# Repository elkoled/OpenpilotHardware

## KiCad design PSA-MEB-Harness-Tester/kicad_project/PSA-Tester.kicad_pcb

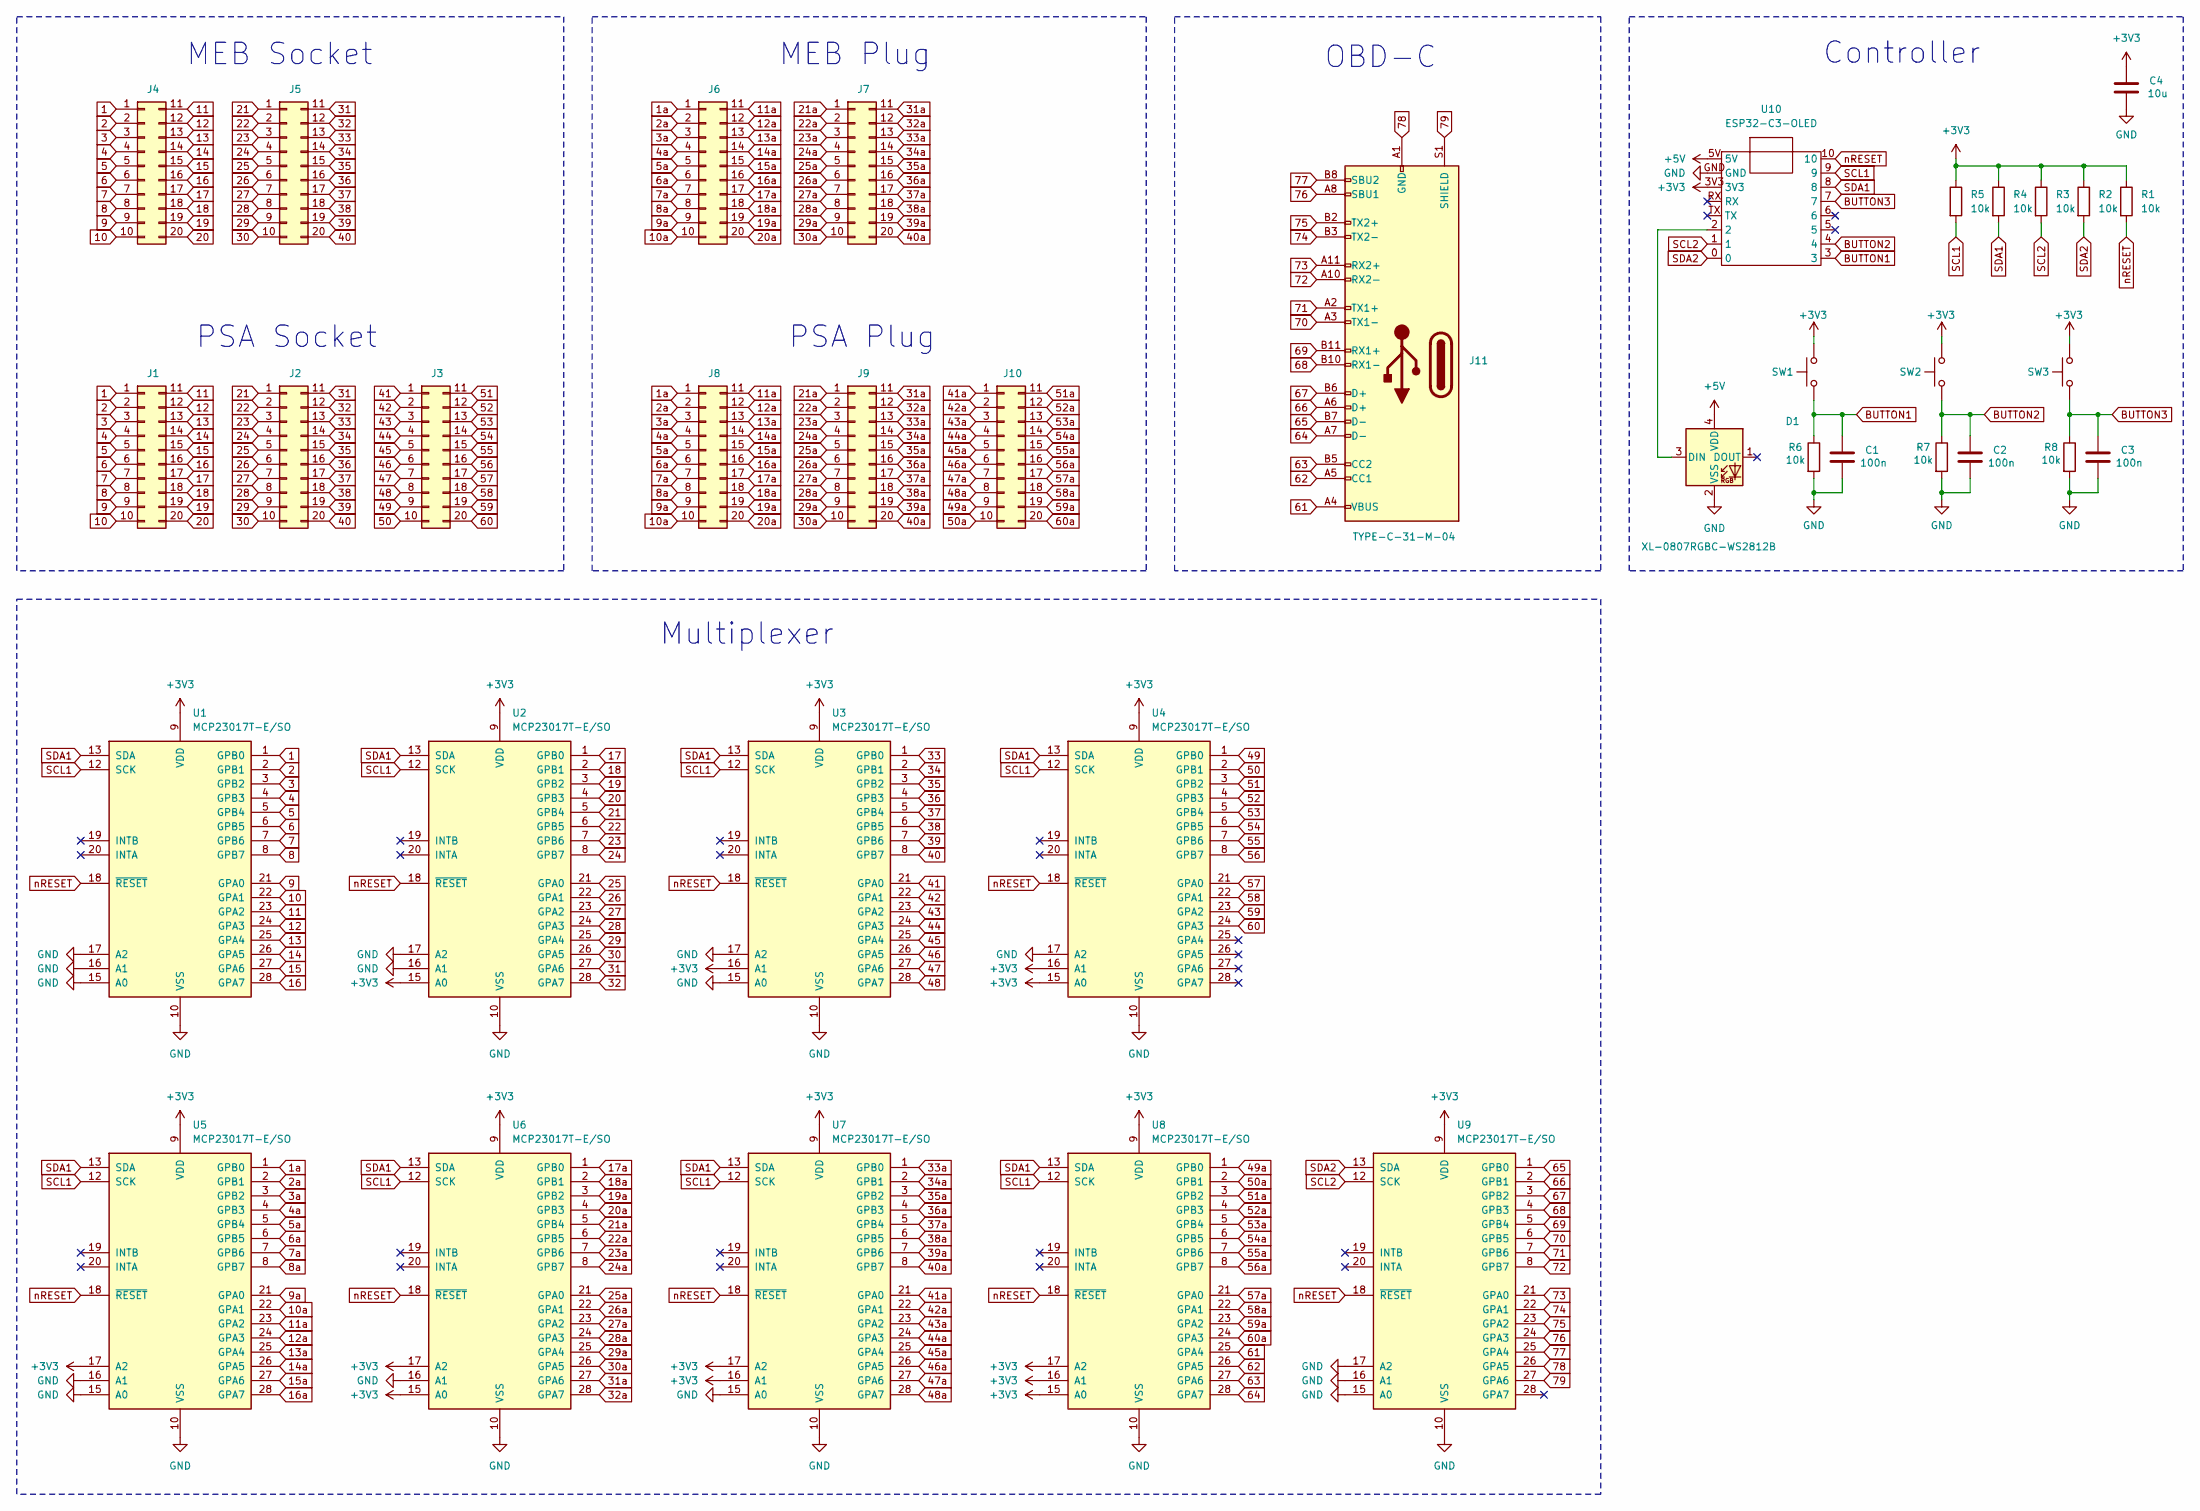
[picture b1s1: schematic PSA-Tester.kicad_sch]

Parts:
C1, C2, C3: 100n; C_1206_3216Metric_Pad1.33x1.80mm_HandSolder
C4: 10u; C_1206_3216Metric_Pad1.33x1.80mm_HandSolder
D1: XL-0807RGBC-WS2812B; LED_WS2812B-2020_PLCC4_2.0x2.0mm
J1, J2, J3, J4, J5, J6, J7, J8, J9, J10: PinHeader_2x10_P2.54mm_Vertical
J11: TYPE-C-31-M-04
R1, R2, R3, R4, R5, R6, R7, R8: 10k; R_1206_3216Metric_Pad1.30x1.75mm_HandSolder
SW1, SW2, SW3: TS-1057S-03126; SW_SPST_Omron_B3FS-101xP
U1, U2, U3, U4, U5, U6, U7, U8, U9: MCP23017T-E/SO; SOIC-28W_7.5x18.7mm_P1.27mm
U10: ESP32-C3-OLED

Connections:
1: J1.1, J4.1, U1.1 (GPB0)
1a: J6.1, J8.1, U5.1 (GPB0)
2: J1.2, J4.2, U1.2 (GPB1)
2a: J6.2, J8.2, U5.2 (GPB1)
3: J1.3, J4.3, U1.3 (GPB2)
3a: J6.3, J8.3, U5.3 (GPB2)
4: J1.4, J4.4, U1.4 (GPB3)
4a: J6.4, J8.4, U5.4 (GPB3)
5: J1.5, J4.5, U1.5 (GPB4)
5a: J6.5, J8.5, U5.5 (GPB4)
6: J1.6, J4.6, U1.6 (GPB5)
6a: J6.6, J8.6, U5.6 (GPB5)
7: J1.7, J4.7, U1.7 (GPB6)
7a: J6.7, J8.7, U5.7 (GPB6)
8: J1.8, J4.8, U1.8 (GPB7)
8a: J6.8, J8.8, U5.8 (GPB7)
9: J1.9, J4.9, U1.21 (GPA0)
9a: J6.9, J8.9, U5.21 (GPA0)
10: J1.10, J4.10, U1.22 (GPA1)
10a: J6.10, J8.10, U5.22 (GPA1)
11: J1.11, J4.11, U1.23 (GPA2)
11a: J6.11, J8.11, U5.23 (GPA2)
12: J1.12, J4.12, U1.24 (GPA3)
12a: J6.12, J8.12, U5.24 (GPA3)
13: J1.13, J4.13, U1.25 (GPA4)
13a: J6.13, J8.13, U5.25 (GPA4)
14: J1.14, J4.14, U1.26 (GPA5)
14a: J6.14, J8.14, U5.26 (GPA5)
15: J1.15, J4.15, U1.27 (GPA6)
15a: J6.15, J8.15, U5.27 (GPA6)
16: J1.16, J4.16, U1.28 (GPA7)
16a: J6.16, J8.16, U5.28 (GPA7)
17: J1.17, J4.17, U2.1 (GPB0)
17a: J6.17, J8.17, U6.1 (GPB0)
18: J1.18, J4.18, U2.2 (GPB1)
18a: J6.18, J8.18, U6.2 (GPB1)
19: J1.19, J4.19, U2.3 (GPB2)
19a: J6.19, J8.19, U6.3 (GPB2)
20: J1.20, J4.20, U2.4 (GPB3)
20a: J6.20, J8.20, U6.4 (GPB3)
21: J2.1, J5.1, U2.5 (GPB4)
21a: J7.1, J9.1, U6.5 (GPB4)
22: J2.2, J5.2, U2.6 (GPB5)
22a: J7.2, J9.2, U6.6 (GPB5)
23: J2.3, J5.3, U2.7 (GPB6)
23a: J7.3, J9.3, U6.7 (GPB6)
24: J2.4, J5.4, U2.8 (GPB7)
24a: J7.4, J9.4, U6.8 (GPB7)
25: J2.5, J5.5, U2.21 (GPA0)
25a: J7.5, J9.5, U6.21 (GPA0)
26: J2.6, J5.6, U2.22 (GPA1)
26a: J7.6, J9.6, U6.22 (GPA1)
27: J2.7, J5.7, U2.23 (GPA2)
27a: J7.7, J9.7, U6.23 (GPA2)
28: J2.8, J5.8, U2.24 (GPA3)
28a: J7.8, J9.8, U6.24 (GPA3)
29: J2.9, J5.9, U2.25 (GPA4)
29a: J7.9, J9.9, U6.25 (GPA4)
30: J2.10, J5.10, U2.26 (GPA5)
30a: J7.10, J9.10, U6.26 (GPA5)
31: J2.11, J5.11, U2.27 (GPA6)
31a: J7.11, J9.11, U6.27 (GPA6)
32: J2.12, J5.12, U2.28 (GPA7)
32a: J7.12, J9.12, U6.28 (GPA7)
33: J2.13, J5.13, U3.1 (GPB0)
33a: J7.13, J9.13, U7.1 (GPB0)
34: J2.14, J5.14, U3.2 (GPB1)
34a: J7.14, J9.14, U7.2 (GPB1)
35: J2.15, J5.15, U3.3 (GPB2)
35a: J7.15, J9.15, U7.3 (GPB2)
36: J2.16, J5.16, U3.4 (GPB3)
36a: J7.16, J9.16, U7.4 (GPB3)
37: J2.17, J5.17, U3.5 (GPB4)
37a: J7.17, J9.17, U7.5 (GPB4)
38: J2.18, J5.18, U3.6 (GPB5)
38a: J7.18, J9.18, U7.6 (GPB5)
39: J2.19, J5.19, U3.7 (GPB6)
39a: J7.19, J9.19, U7.7 (GPB6)
40: J2.20, J5.20, U3.8 (GPB7)
40a: J7.20, J9.20, U7.8 (GPB7)
41: J3.1, U3.21 (GPA0)
41a: J10.1, U7.21 (GPA0)
42: J3.2, U3.22 (GPA1)
42a: J10.2, U7.22 (GPA1)
43: J3.3, U3.23 (GPA2)
43a: J10.3, U7.23 (GPA2)
44: J3.4, U3.24 (GPA3)
44a: J10.4, U7.24 (GPA3)
45: J3.5, U3.25 (GPA4)
45a: J10.5, U7.25 (GPA4)
46: J3.6, U3.26 (GPA5)
46a: J10.6, U7.26 (GPA5)
47: J3.7, U3.27 (GPA6)
47a: J10.7, U7.27 (GPA6)
48: J3.8, U3.28 (GPA7)
48a: J10.8, U7.28 (GPA7)
49: J3.9, U4.1 (GPB0)
49a: J10.9, U8.1 (GPB0)
50: J3.10, U4.2 (GPB1)
50a: J10.10, U8.2 (GPB1)
51: J3.11, U4.3 (GPB2)
51a: J10.11, U8.3 (GPB2)
52: J3.12, U4.4 (GPB3)
52a: J10.12, U8.4 (GPB3)
53: J3.13, U4.5 (GPB4)
53a: J10.13, U8.5 (GPB4)
54: J3.14, U4.6 (GPB5)
54a: J10.14, U8.6 (GPB5)
55: J3.15, U4.7 (GPB6)
55a: J10.15, U8.7 (GPB6)
56: J3.16, U4.8 (GPB7)
56a: J10.16, U8.8 (GPB7)
57: J3.17, U4.21 (GPA0)
57a: J10.17, U8.21 (GPA0)
58: J3.18, U4.22 (GPA1)
58a: J10.18, U8.22 (GPA1)
59: J3.19, U4.23 (GPA2)
59a: J10.19, U8.23 (GPA2)
60: J3.20, U4.24 (GPA3)
60a: J10.20, U8.24 (GPA3)
61: J11.A4 (VBUS), J11.A9 (VBUS), J11.B4 (VBUS), J11.B9 (VBUS), U8.25 (GPA4)
62: J11.A5 (CC1), U8.26 (GPA5)
63: J11.B5 (CC2), U8.27 (GPA6)
64: J11.A7 (D-), U8.28 (GPA7)
65: J11.B7 (D-), U9.1 (GPB0)
66: J11.A6 (D+), U9.2 (GPB1)
67: J11.B6 (D+), U9.3 (GPB2)
68: J11.B10 (RX1-), U9.4 (GPB3)
69: J11.B11 (RX1+), U9.5 (GPB4)
70: J11.A3 (TX1-), U9.6 (GPB5)
71: J11.A2 (TX1+), U9.7 (GPB6)
72: J11.A10 (RX2-), U9.8 (GPB7)
73: J11.A11 (RX2+), U9.21 (GPA0)
74: J11.B3 (TX2-), U9.22 (GPA1)
75: J11.B2 (TX2+), U9.23 (GPA2)
76: J11.A8 (SBU1), U9.24 (GPA3)
77: J11.B8 (SBU2), U9.25 (GPA4)
78: J11.A1 (GND), J11.A12 (GND), J11.B1 (GND), J11.B12 (GND), U9.26 (GPA5)
79: J11.S1 (SHIELD), U9.27 (GPA6)
+3V3: C4.1, R1.1, R2.1, R3.1, R4.1, R5.1, SW1.1, SW2.1, SW3.1, U1.9 (VDD), U2.9 (VDD), U2.15 (A0), U3.9 (VDD), U3.16 (A1), U4.9 (VDD), U4.15 (A0), U4.16 (A1), U5.9 (VDD), U5.17 (A2), U6.9 (VDD), U6.15 (A0), U6.17 (A2), U7.9 (VDD), U7.16 (A1), U7.17 (A2), U8.9 (VDD), U8.15 (A0), U8.16 (A1), U8.17 (A2), U9.9 (VDD), U10.3V3
+5V: D1.4 (VDD), U10.5V
BUTTON1: C1.1, R6.1, SW1.2, U10.3
BUTTON2: C2.1, R7.1, SW2.2, U10.4
BUTTON3: C3.1, R8.1, SW3.2, U10.7
GND: C1.2, C2.2, C3.2, C4.2, D1.2 (VSS), R6.2, R7.2, R8.2, U1.10 (VSS), U1.15 (A0), U1.16 (A1), U1.17 (A2), U2.10 (VSS), U2.16 (A1), U2.17 (A2), U3.10 (VSS), U3.15 (A0), U3.17 (A2), U4.10 (VSS), U4.17 (A2), U5.10 (VSS), U5.15 (A0), U5.16 (A1), U6.10 (VSS), U6.16 (A1), U7.10 (VSS), U7.15 (A0), U8.10 (VSS), U9.10 (VSS), U9.15 (A0), U9.16 (A1), U9.17 (A2), U10.GND
unnamed: D1.3 (DIN), U10.2
SCL1: R5.2, U1.12 (SCK), U2.12 (SCK), U3.12 (SCK), U4.12 (SCK), U5.12 (SCK), U6.12 (SCK), U7.12 (SCK), U8.12 (SCK), U10.9
SCL2: R3.2, U9.12 (SCK), U10.1
SDA1: R4.2, U1.13 (SDA), U2.13 (SDA), U3.13 (SDA), U4.13 (SDA), U5.13 (SDA), U6.13 (SDA), U7.13 (SDA), U8.13 (SDA), U10.8
SDA2: R2.2, U9.13 (SDA), U10.0
nRESET: R1.2, U1.18 (~RESET), U2.18 (~RESET), U3.18 (~RESET), U4.18 (~RESET), U5.18 (~RESET), U6.18 (~RESET), U7.18 (~RESET), U8.18 (~RESET), U9.18 (~RESET), U10.10

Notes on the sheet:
Controller
OBD-C
Multiplexer
PSA Plug
MEB Plug
MEB Socket
PSA Socket

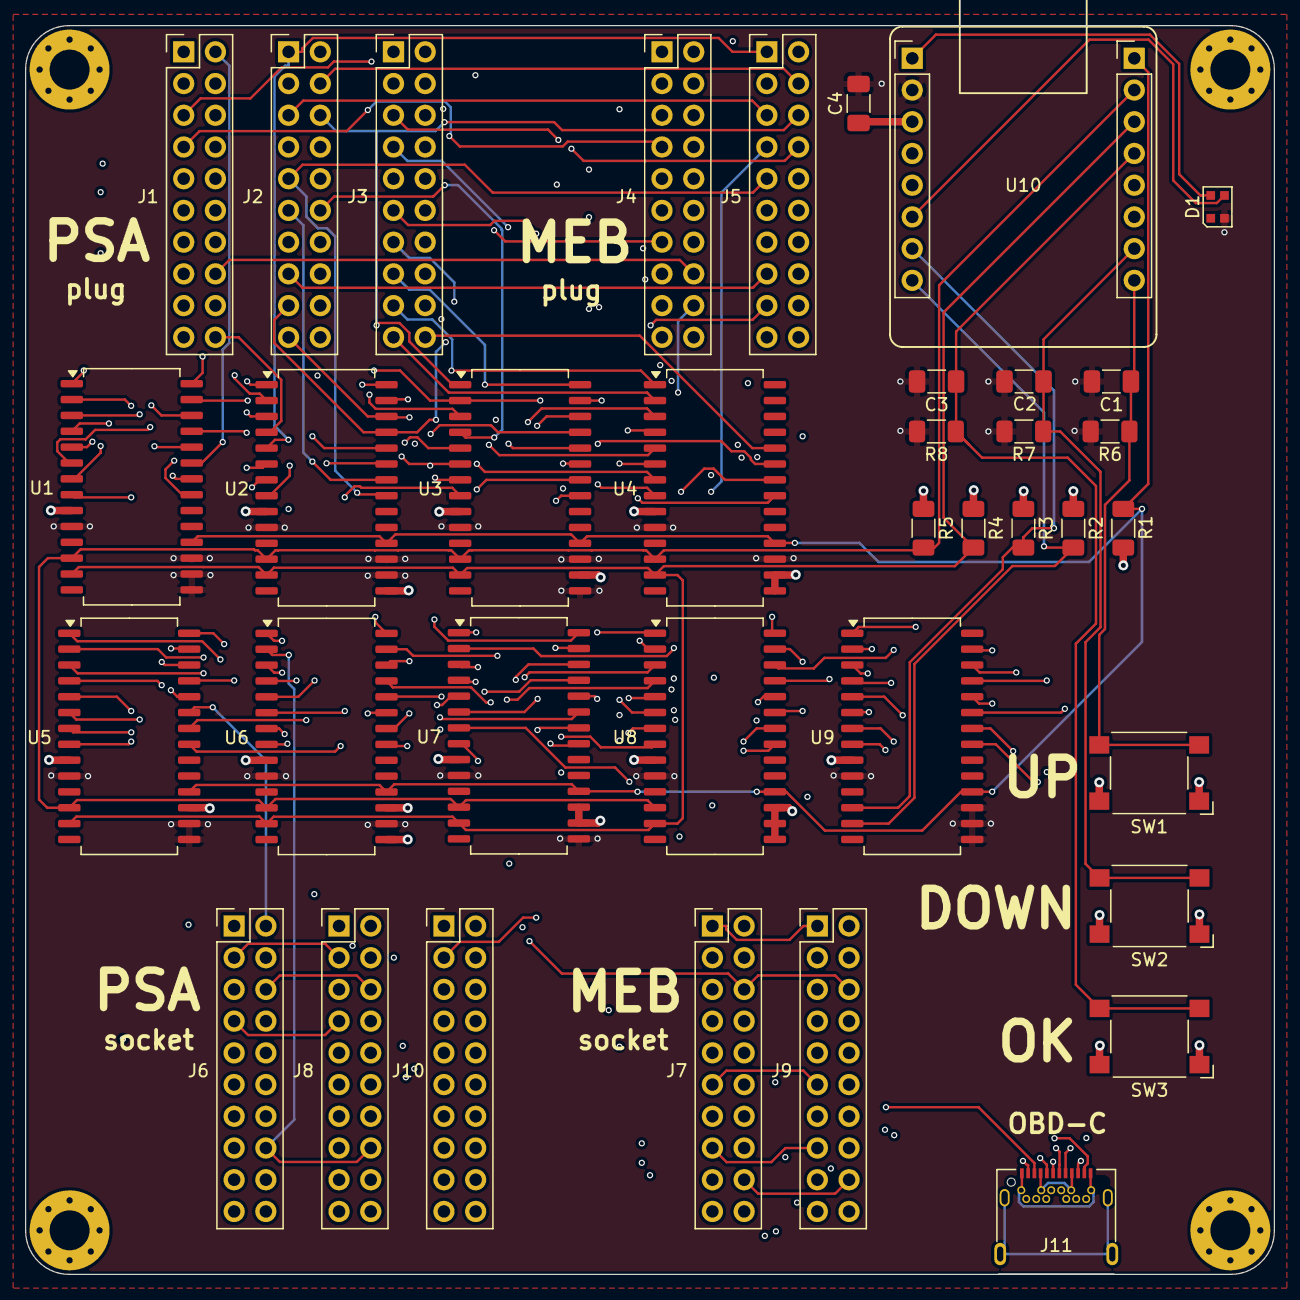
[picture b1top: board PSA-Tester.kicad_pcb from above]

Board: 4 copper layers, 100.0 x 100.0 mm, 41 parts (0 on the bottom side), 151 nets.

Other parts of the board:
REF1, REF2, REF3, REF4: MountingHole_3.2mm_M3_Pad_Via

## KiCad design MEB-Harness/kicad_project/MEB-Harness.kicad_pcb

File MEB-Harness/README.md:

# Open Source All-in-One Harness / Harnessbox for VW MEB-based vehicles equipped with a Gateway

## Compatibility list
#### Volkswagen
- ID.3
- ID.4
- ID.5
- ID.6
- ID.7
- ID.7 Tourer
- ID. Buzz
- ID. Buzz Cargo
- ID. UNYX
#### Škoda
- Enyaq
- Enyaq Coupé
- Elroq
#### Cupra
- Born
- Tavascan

The device is in development

If you have any questions contact me on Discord: elkoled

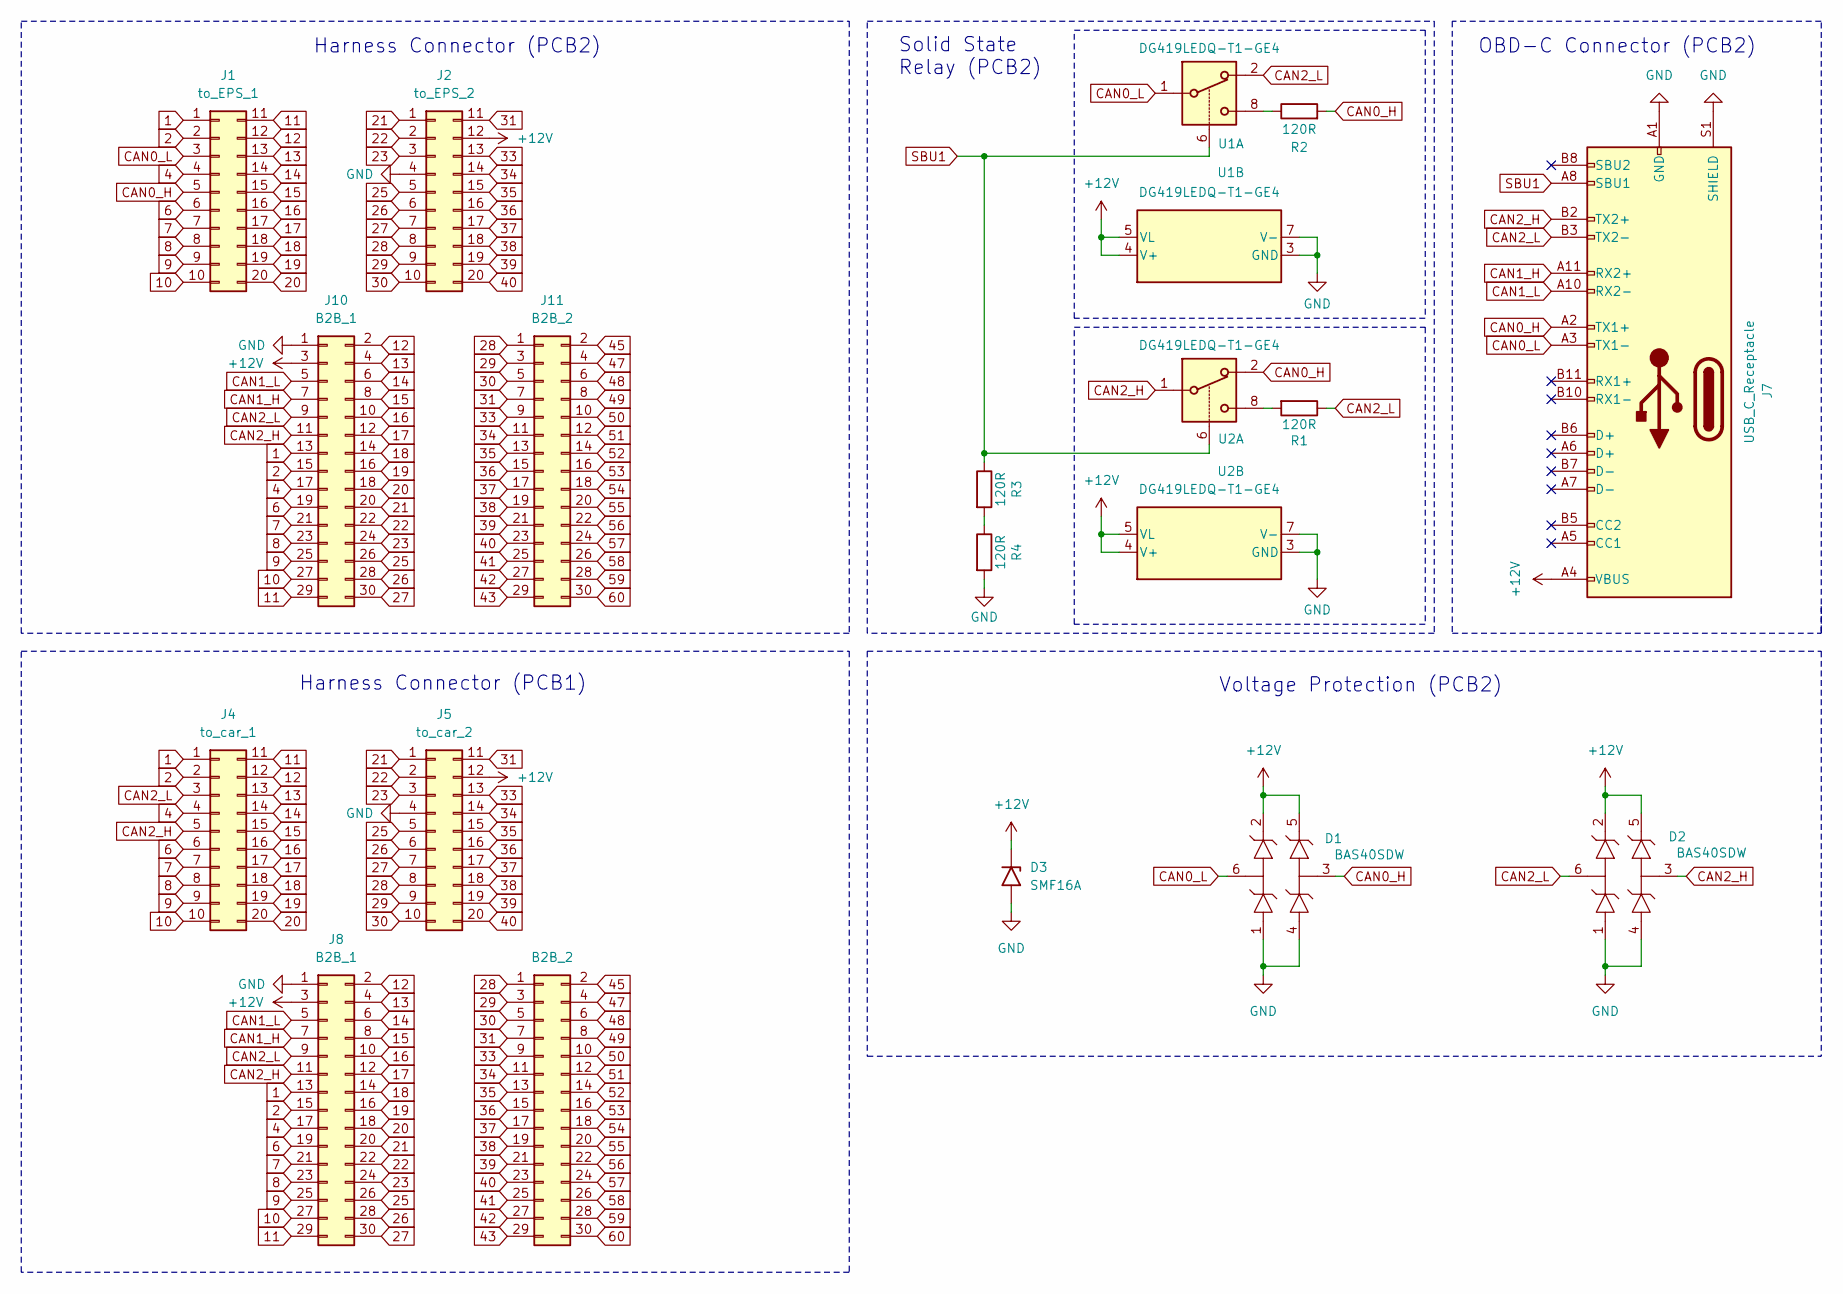
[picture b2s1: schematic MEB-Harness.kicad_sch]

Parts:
D1, D2: BAS40SDW; SOT-363_SC-70-6
D3: SMF16A; D_SOD-123
J1: to_EPS_1; Amphenol_10129381-920003BLF
J2: to_EPS_2; Amphenol_10129381-920003BLF
J4: to_car_1; SAMTEC_ESW-110-44-F-D
J5: to_car_2; SAMTEC_ESW-110-44-F-D
J7: USB_C_Receptacle; GCT_USB4115-03-C_REVB4
J8, J10: B2B_1; SAMTEC_TW-10-03-T-T-320-100
J9, J11: B2B_2; SAMTEC_TW-10-03-T-T-320-100
R1, R2, R3, R4: 120R; R_1206_3216Metric
U1, U2: DG419LEDQ-T1-GE4; SOIC-8_3.9x4.9mm_P1.27mm

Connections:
1: J1.1, J4.1, J8.13, J10.13
2: J1.2, J4.2, J8.15, J10.15
4: J1.4, J4.4, J8.17, J10.17
6: J1.6, J4.6, J8.19, J10.19
7: J1.7, J4.7, J8.21, J10.21
8: J1.8, J4.8, J8.23, J10.23
9: J1.9, J4.9, J8.25, J10.25
10: J1.10, J4.10, J8.27, J10.27
11: J1.11, J4.11, J8.29, J10.29
12: J1.12, J4.12, J8.2, J10.2
13: J1.13, J4.13, J8.4, J10.4
14: J1.14, J4.14, J8.6, J10.6
15: J1.15, J4.15, J8.8, J10.8
16: J1.16, J4.16, J8.10, J10.10
17: J1.17, J4.17, J8.12, J10.12
18: J1.18, J4.18, J8.14, J10.14
19: J1.19, J4.19, J8.16, J10.16
20: J1.20, J4.20, J8.18, J10.18
21: J2.1, J5.1, J8.20, J10.20
22: J2.2, J5.2, J8.22, J10.22
23: J2.3, J5.3, J8.24, J10.24
25: J2.5, J5.5, J8.26, J10.26
26: J2.6, J5.6, J8.28, J10.28
27: J2.7, J5.7, J8.30, J10.30
28: J2.8, J5.8, J9.1, J11.1
29: J2.9, J5.9, J9.3, J11.3
30: J2.10, J5.10, J9.5, J11.5
31: J2.11, J5.11, J9.7, J11.7
33: J2.13, J5.13, J9.9, J11.9
34: J2.14, J5.14, J9.11, J11.11
35: J2.15, J5.15, J9.13, J11.13
36: J2.16, J5.16, J9.15, J11.15
37: J2.17, J5.17, J9.17, J11.17
38: J2.18, J5.18, J9.19, J11.19
39: J2.19, J5.19, J9.21, J11.21
40: J2.20, J5.20, J9.23, J11.23
41: J9.25, J11.25
42: J9.27, J11.27
43: J9.29, J11.29
45: J9.2, J11.2
47: J9.4, J11.4
48: J9.6, J11.6
49: J9.8, J11.8
50: J9.10, J11.10
51: J9.12, J11.12
52: J9.14, J11.14
53: J9.16, J11.16
54: J9.18, J11.18
55: J9.20, J11.20
56: J9.22, J11.22
57: J9.24, J11.24
58: J9.26, J11.26
59: J9.28, J11.28
60: J9.30, J11.30
+12V: D1.2, D1.5, D2.2, D2.5, D3.1 (A1), J2.12, J5.12, J7.A4 (VBUS), J7.A9 (VBUS), J7.B4 (VBUS), J7.B9 (VBUS), J8.3, J10.3, U1.4 (V+), U1.5 (VL), U2.4 (V+), U2.5 (VL)
CAN0_H: D1.3, J1.5, J7.A2 (TX1+), R2.2, U2.2
CAN0_L: D1.6, J1.3, J7.A3 (TX1-), U1.1
CAN1_H: J7.A11 (RX2+), J8.7, J10.7
CAN1_L: J7.A10 (RX2-), J8.5, J10.5
CAN2_H: D2.3, J4.5, J7.B2 (TX2+), J8.11, J10.11, U2.1
CAN2_L: D2.6, J4.3, J7.B3 (TX2-), J8.9, J10.9, R1.1, U1.2
GND: D1.1, D1.4, D2.1, D2.4, D3.2 (A2), J2.4, J5.4, J7.A1 (GND), J7.A12 (GND), J7.B1 (GND), J7.B12 (GND), J7.S1 (SHIELD), J8.1, J10.1, R4.2, U1.3 (GND), U1.7 (V-), U2.3 (GND), U2.7 (V-)
unnamed: R1.2, U2.8
unnamed: R2.1, U1.8
unnamed: R3.2, R4.1
SBU1: J7.A8 (SBU1), R3.1, U1.6, U2.6

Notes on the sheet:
Harness Connector (PCB2)
Voltage Protection (PCB2)
OBD-C Connector (PCB2)
Solid State Relay (PCB2)
Harness Connector (PCB1)

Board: 4 copper layers, 18 parts (8 on the bottom side), 66 nets, no tracks yet.

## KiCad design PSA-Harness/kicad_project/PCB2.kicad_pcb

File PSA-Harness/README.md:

# Open Source PSA All in One Harness / Harnessbox for Peugeot, Citroen, Opel, Vauxhall, DS Cars
The device is in development

If you have any questions contact me on Discord: elkoled

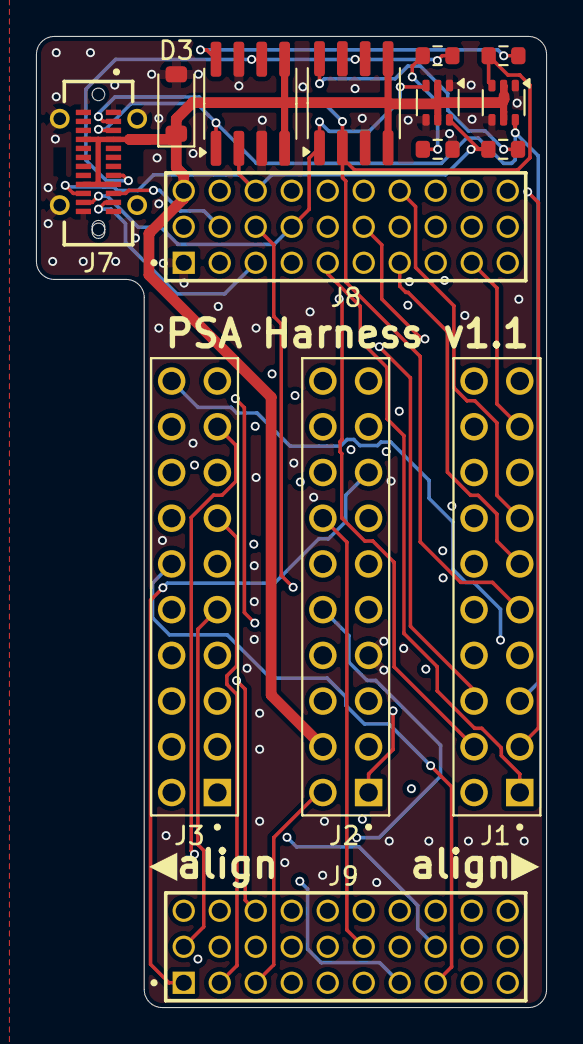
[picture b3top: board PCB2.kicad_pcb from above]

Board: 4 copper layers, 28.3 x 54.0 mm, 15 parts (0 on the bottom side), 66 nets.

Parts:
D1, D2: BAS40SDW-AU_R1_000A1; SOT-363_SC-70-6
D3: C353308; D_SOD-123
J1, J2, J3: PH-01481; 10129381-920003BLF
J7: TYPE-C-31-M-07; GCT_USB4115-03-C_REVB4
J8: B2B_1; SAMTEC_TW-10-X-X-T-X-X
J9: B2B_2; SAMTEC_TW-10-X-X-T-X-X
R1, R2, R3, R4: CRCW0603120RFKEAHP; R_0603_1608Metric
U1, U2: DG419LEDY-T1-GE4; SOIC-8_3.9x4.9mm_P1.27mm

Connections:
1: J1.1, J8.13
2: J1.2, J8.15
4: J1.4, J8.17
6: J1.6, J8.19
7: J1.7, J8.21
8: J1.8, J8.23
9: J1.9, J8.25
10: J1.10, J8.27
11: J1.11, J8.29
12: J1.12, J8.2
13: J1.13, J8.4
14: J1.14, J8.6
15: J1.15, J8.8
16: J1.16, J8.10
17: J1.17, J8.12
18: J1.18, J8.14
19: J1.19, J8.16
20: J1.20, J8.18
21: J2.1, J8.20
22: J2.2, J8.22
23: J2.3, J8.24
25: J2.5, J8.26
26: J2.6, J8.28
27: J2.7, J8.30
28: J2.8, J9.1
29: J2.9, J9.3
30: J2.10, J9.5
31: J2.11, J9.7
33: J2.13, J9.9
34: J2.14, J9.11
35: J2.15, J9.13
36: J2.16, J9.15
37: J2.17, J9.17
38: J2.18, J9.19
39: J2.19, J9.21
40: J2.20, J9.23
41: J3.1, J9.25
42: J3.2, J9.27
43: J3.3, J9.29
45: J3.5, J9.2
47: J3.7, J9.4
48: J3.8, J9.6
49: J3.9, J9.8
50: J3.10, J9.10
51: J3.11, J9.12
52: J3.12, J9.14
53: J3.13, J9.16
54: J3.14, J9.18
55: J3.15, J9.20
56: J3.16, J9.22
57: J3.17, J9.24
58: J3.18, J9.26
59: J3.19, J9.28
60: J3.20, J9.30
+12V: D1.2, D1.5, D2.2, D2.5, D3.1 (A1), J2.12, J7.A4 (VBUS), J7.A9 (VBUS), J7.B4 (VBUS), J7.B9 (VBUS), J8.3, U1.4 (V+), U1.5 (VL), U2.4 (V+), U2.5 (VL)
CAN0_H: D1.3, J1.5, J7.A2 (TX1+), R2.2, U2.2
CAN0_L: D1.6, J1.3, J7.A3 (TX1-), U1.1
CAN1_H: J3.6, J7.A11 (RX2+), J8.7
CAN1_L: J3.4, J7.A10 (RX2-), J8.5
CAN2_H: D2.3, J7.B2 (TX2+), J8.11, U2.1
CAN2_L: D2.6, J7.B3 (TX2-), J8.9, R1.1, U1.2
GND: D1.1, D1.4, D2.1, D2.4, D3.2 (A2), J2.4, J7.A1 (GND), J7.A12 (GND), J7.B1 (GND), J7.B12 (GND), J7.S1 (SHIELD), J8.1, R4.2, U1.3 (GND), U1.7 (V-), U2.3 (GND), U2.7 (V-)
unnamed: R1.2, U2.8
unnamed: R2.1, U1.8
unnamed: R3.2, R4.1
SBU1: J7.A8 (SBU1), R3.1, U1.6, U2.6

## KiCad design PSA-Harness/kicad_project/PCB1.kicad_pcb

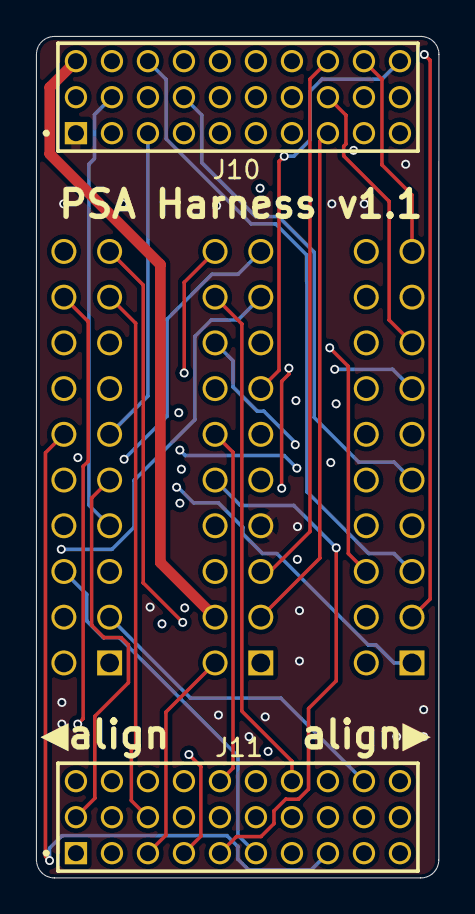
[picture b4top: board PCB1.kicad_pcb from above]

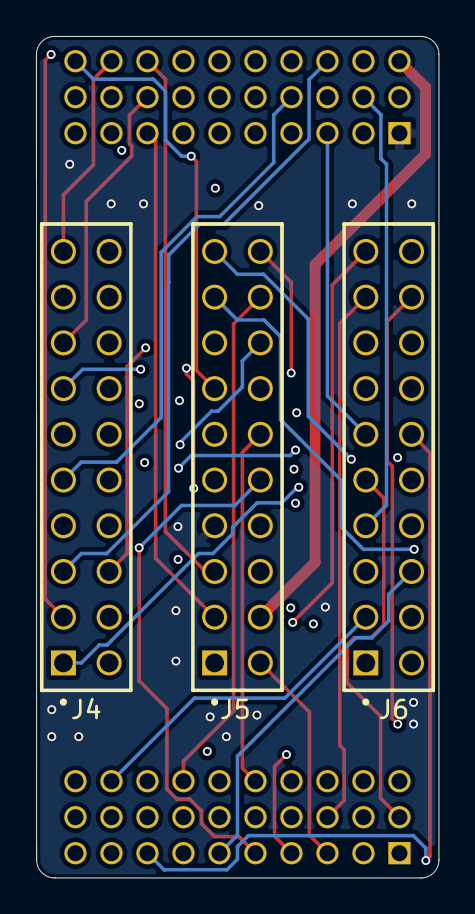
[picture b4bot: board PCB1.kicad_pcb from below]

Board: 4 copper layers, 22.4 x 46.8 mm, 5 parts (3 on the bottom side), 60 nets.

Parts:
J4: to_car_1; ESW-110-44-F-D
J5: to_car_2; ESW-110-44-F-D
J6: to_car_3; ESW-110-44-F-D
J10: B2B_1; SAMTEC_TW-10-X-X-T-X-X
J11: B2B_2; SAMTEC_TW-10-X-X-T-X-X

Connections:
1: J4.1, J10.13
2: J4.2, J10.15
4: J4.4, J10.17
6: J4.6, J10.19
7: J4.7, J10.21
8: J4.8, J10.23
9: J4.9, J10.25
10: J4.10, J10.27
11: J4.11, J10.29
12: J4.12, J10.2
13: J4.13, J10.4
14: J4.14, J10.6
15: J4.15, J10.8
16: J4.16, J10.10
17: J4.17, J10.12
18: J4.18, J10.14
19: J4.19, J10.16
20: J4.20, J10.18
21: J5.1, J10.20
22: J5.2, J10.22
23: J5.3, J10.24
25: J5.5, J10.26
26: J5.6, J10.28
27: J5.7, J10.30
28: J5.8, J11.1
29: J5.9, J11.3
30: J5.10, J11.5
31: J5.11, J11.7
33: J5.13, J11.9
34: J5.14, J11.11
35: J5.15, J11.13
36: J5.16, J11.15
37: J5.17, J11.17
38: J5.18, J11.19
39: J5.19, J11.21
40: J5.20, J11.23
41: J6.1, J11.25
42: J6.2, J11.27
43: J6.3, J11.29
45: J6.5, J11.2
47: J6.7, J11.4
48: J6.8, J11.6
49: J6.9, J11.8
50: J6.10, J11.10
51: J6.11, J11.12
52: J6.12, J11.14
53: J6.13, J11.16
54: J6.14, J11.18
55: J6.15, J11.20
56: J6.16, J11.22
57: J6.17, J11.24
58: J6.18, J11.26
59: J6.19, J11.28
60: J6.20, J11.30
+12V: J5.12, J10.3
CAN1_H: J6.6, J10.7
CAN1_L: J6.4, J10.5
CAN2_H: J4.5, J10.11
CAN2_L: J4.3, J10.9
GND: J5.4, J10.1

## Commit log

2025-05-01 add: PSA Harness
2025-05-01 chg: add doc images, upgrade to kicad 9
2025-05-01 chg: use correct footprints, SMD socket clearence too low
2025-05-01 chg: stacked PCBs
2025-05-01 reduce clearances
2025-05-01 add: rendering
2025-05-02 add: connector footprints
2025-05-02 chg: reduce clearances to 0.1mm
2025-05-02 chg: save as individual PCBs
2025-05-02 PCB1 routed, PCB2 partly routed
2025-05-02 chg: rearrange pcb interconnect pins
2025-05-02 PCB1 routed, PCB2 partly
2025-05-02 PCB1+2 routed
2025-05-03 add: raw plug 3d-scans
2025-05-03 chg: final PCB shape
2025-05-03 cleared DRC errors
2025-05-03 add: PCB renderings
2025-05-03 add: oshw logo
2025-05-03 chg: schematic: use solid state relay
2025-05-03 chg: schematic done
2025-05-03 chg: components placed
2025-05-03 DRC ok
2025-05-03 update clearance rules
2025-05-03 modify pinsocket layout for inner layers to route
2025-05-03 good DRC settings
2025-05-03 separate PCB1/2
2025-05-03 CAN routing PCB1
2025-05-03 more clearance test
2025-05-03 PCB1 routed
2025-05-03 PCB2 CAN routed
2025-05-03 PCB2 routed
2025-05-03 improve PCB2 clearences
2025-05-03 add: Schematic export
2025-05-04 improve PCB1 clearences
2025-05-04 add: pictures, cable harness doc
2025-05-04 add: html BOM
2025-05-04 add: layout pictures
2025-05-06 cable-board setup
2025-05-06 components placed
2025-05-07 components variant 2
2025-05-07 cleanup doc files
2025-05-07 components placed exactly
2025-05-07 CAN routed
2025-05-07 board routed
2025-05-07 move to_car connector to back side
2025-05-07 add pictures and step
2025-05-08 add: alternative connectors
2025-05-08 chg: alternative connector DRC OK
2025-05-08 chg: separate PCB1/2
2025-05-08 PCB1/2 routed
2025-05-08 fix DRC errors
2025-05-08 add: BOM
2025-05-08 add: docs
2025-05-08 add: comma harness for reference
2025-05-08 use other USB-C connector
2025-05-08 move usb-c connector to back side
2025-05-10 chg: decrease PCB2 USB-C section size by 0.6mm
2025-05-11 chg: fix component names
2025-06-03 add rendering
2025-06-03 add: step file
2025-06-03 add STLs
2025-06-03 remove BOM
2025-06-15 change footprint of analog switch from msop to soic
2025-06-15 change footprint of analog switch from msop to soic on pcb2
2025-06-15 PCB1 add up indicator
2025-06-15 PCB2 add up indicator
2025-06-15 add BOM
2025-06-15 fix DFM
2025-06-15 use bom component names
2025-06-15 add manufacturing zip
2025-06-24 add tester project
2025-06-24 initial tester schematic done
2025-06-24 initial tester pcb
2025-06-24 swap mux footprint to DIP-28
2025-06-24 still 6 unrouted
2025-06-25 routed with SMD packages
2025-06-25 100x100mm routed
2025-06-25 part fixes
2025-06-25 add RGB LED
2025-06-25 add texts
2025-06-25 partly routed
2025-06-25 routed
2025-06-25 fixes
2025-06-25 usb-c footprint fix
2025-06-25 add tester pcb production
2025-06-30 revert usb-c footprint, add 3d models
2025-06-30 change usb-c type and button
2025-06-30 add tester pcb production data
2025-06-30 fix DRC
2025-07-02 fix pin5/pin6 used by I2C OLED
2025-07-03 add README for MEB-Harness
2025-07-07 add MEB Harness project
2025-07-11 adjust PSA-Harness housing for longer USB-C connector
2025-07-11 adjust latch for top housing part
2025-07-14 change folder structure, add platformio project
2025-07-14 implement MCP23017 driver
2025-07-14 add mapping
2025-07-15 add is_plug mapping
2025-07-15 add test routine
2025-07-15 clean
2025-07-15 test cycle all pins
2025-07-15 fix mapping
2025-07-15 fix socket-plug names
2025-07-16 fix PSA-Tester swapped pin headers
2025-07-16 swap switches, move sockets 4mm right
2025-07-16 align tester board settings to psa-harness
2025-07-16 PSA-Tester partly routed
2025-07-16 add GND vias
2025-07-16 add usb-c routing
2025-07-17 ordered Tester PCB
2025-07-17 add tester gerber
2025-07-19 adjust lever to fit 2023+ BSI
2025-11-13 move all psa harness components to top layer
2025-11-13 CAN signals routed
2025-11-13 update pcb_1 gerber
2025-11-13 routed power
2025-11-13 pcb2 fixed drc
2025-11-14 change pcb2 to jlc parts
2025-11-14 pcb2 gerber export
2025-11-29 add psa tester housing
2025-12-08 update top harness STL
2026-01-03 update harness tester with fixed PCB
2026-01-03 write pattern to outputs
